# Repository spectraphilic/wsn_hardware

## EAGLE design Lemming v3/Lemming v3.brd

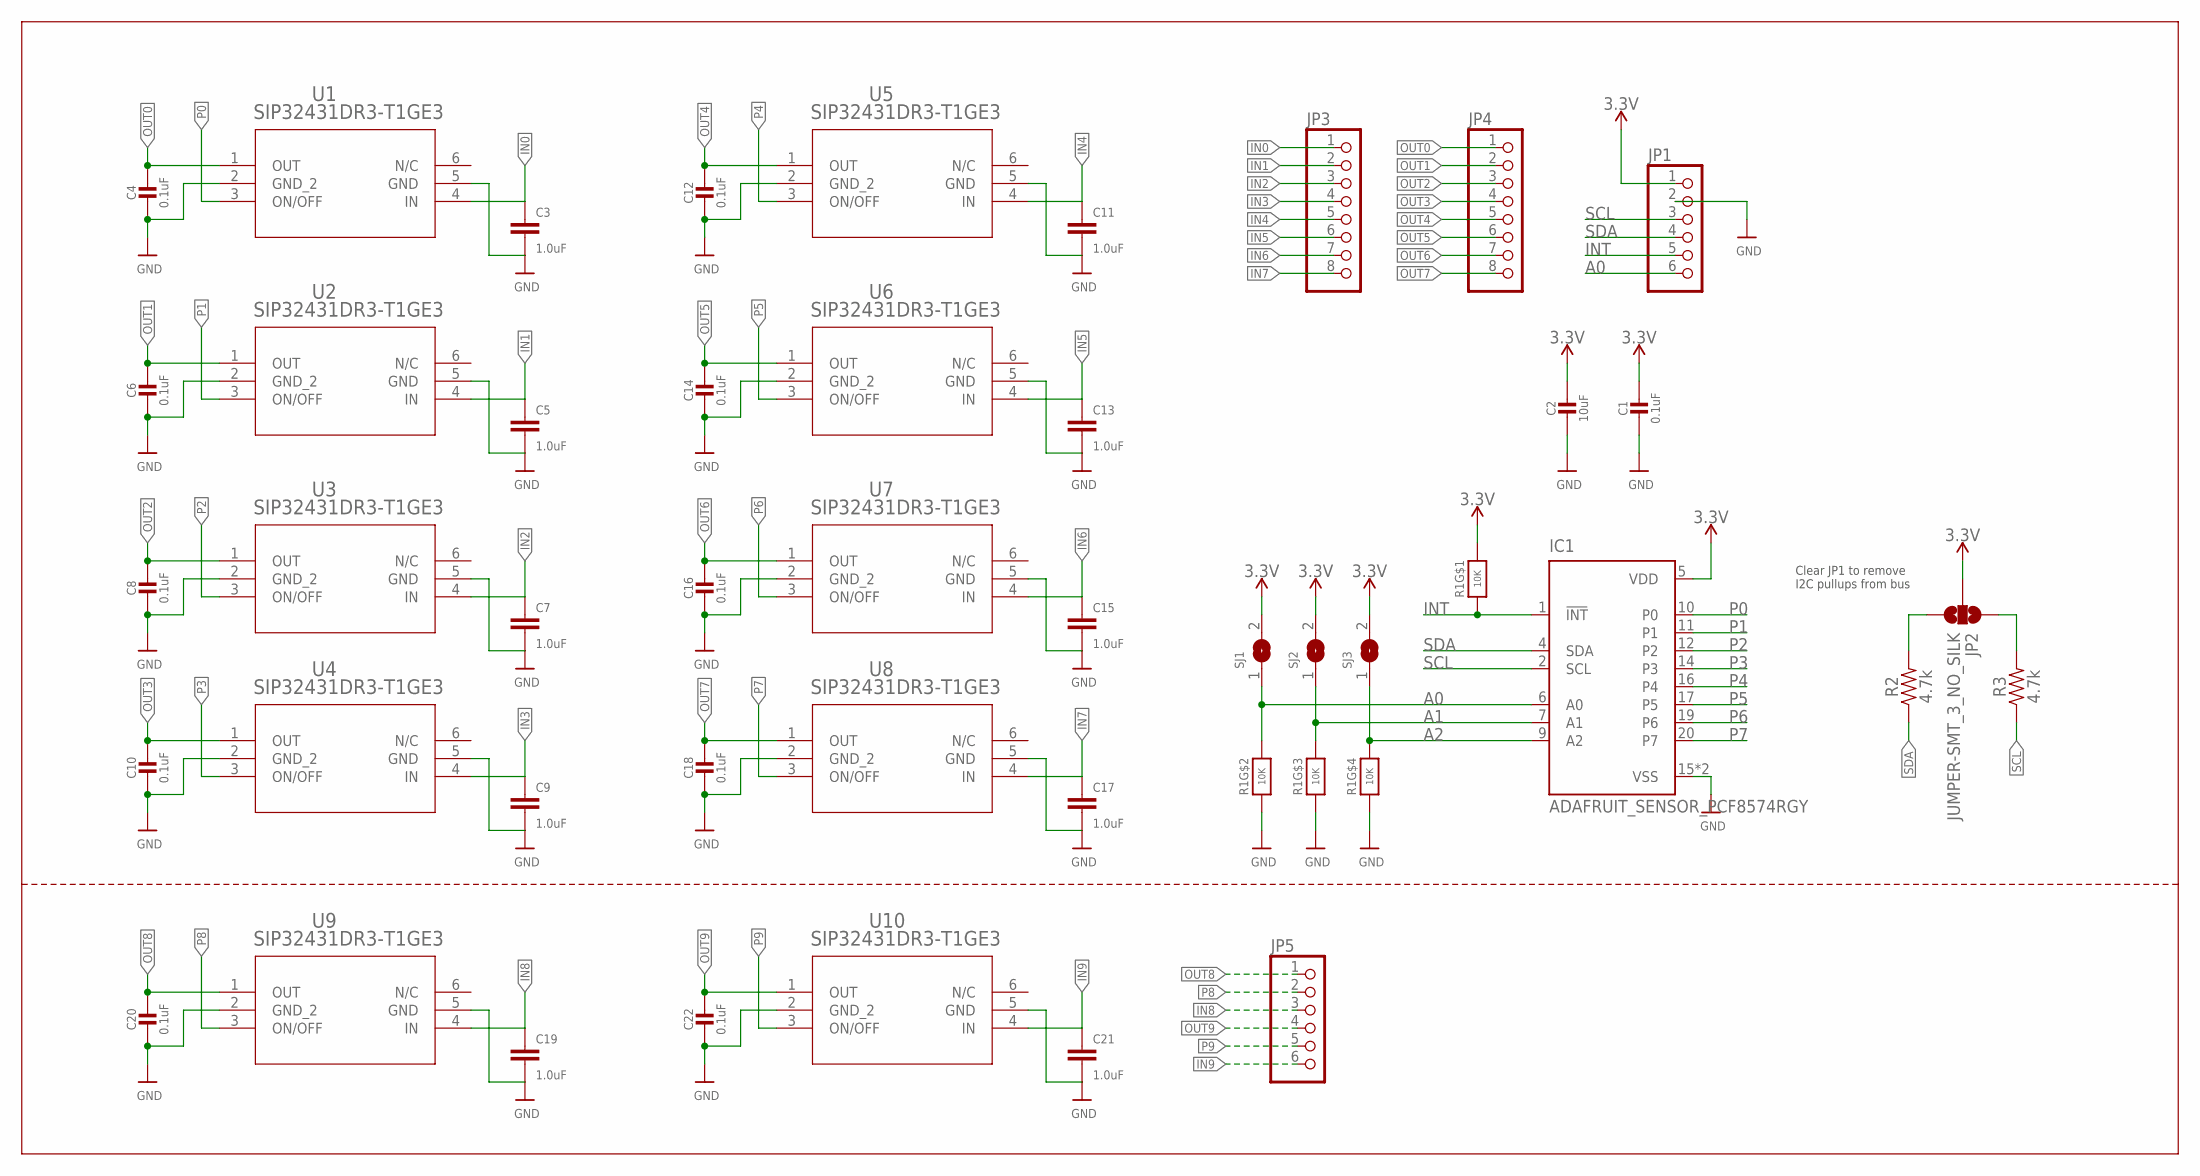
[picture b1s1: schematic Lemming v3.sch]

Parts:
C1, C4, C6, C8, C10, C12, C14, C16, C18, C20, C22: 0.1uF; 0603-NO
C2: 10uF; 0805-NO
C3, C5, C7, C9, C11, C13, C15, C17, C19, C21: 1.0uF; 0603
IC1: ADAFRUIT_SENSOR_PCF8574RGY; ADAFRUIT_SENSOR_VQFN20_3.5X4.5
JP1, JP5: HEADER-1X670MIL; 1X06_ROUND_70
JP2: JUMPER-SMT_3_NO_SILK; SMT-JUMPER_3_NO_SILK
JP3, JP4: PINHD-1X8BIG; 1X08-BIG
R1: 10K; MICROBUILDER_RESPACK_4X0603
R2, R3: 4.7k; 0603
SJ1, SJ2, SJ3: SOLDERJUMPER; SOLDERJUMPER_ARROW_NOPASTE
U1, U2, U3, U4, U5, U6, U7, U8, U9, U10: SIP32431DR3-T1GE3; SC-70-6_VIS

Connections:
3.3V: C1.1, C2.1, IC1.5 (VDD), JP1.1, JP2.2, R1.8 (2), SJ1.2, SJ2.2, SJ3.2
A0: IC1.6 (A0), JP1.6, R1.7 (2), SJ1.1
A1: IC1.7 (A1), R1.6 (2), SJ2.1
A2: IC1.9 (A2), R1.5 (2), SJ3.1
GND: C1.2, C2.2, C3.2, C4.2, C5.2, C6.2, C7.2, C8.2, C9.2, C10.2, C11.2, C12.2, C13.2, C14.2, C15.2, C16.2, C17.2, C18.2, C19.2, C20.2, C21.2, C22.2, IC1.15 (VSS), IC1.21 (VSS), JP1.2, R1.2 (1), R1.3 (1), R1.4 (1), U1.2 (GND_2), U1.5 (GND), U2.2 (GND_2), U2.5 (GND), U3.2 (GND_2), U3.5 (GND), U4.2 (GND_2), U4.5 (GND), U5.2 (GND_2), U5.5 (GND), U6.2 (GND_2), U6.5 (GND), U7.2 (GND_2), U7.5 (GND), U8.2 (GND_2), U8.5 (GND), U9.2 (GND_2), U9.5 (GND), U10.2 (GND_2), U10.5 (GND)
IN0: C3.1, JP3.1, U1.4 (IN)
IN1: C5.1, JP3.2, U2.4 (IN)
IN2: C7.1, JP3.3, U3.4 (IN)
IN3: C9.1, JP3.4, U4.4 (IN)
IN4: C11.1, JP3.5, U5.4 (IN)
IN5: C13.1, JP3.6, U6.4 (IN)
IN6: C15.1, JP3.7, U7.4 (IN)
IN7: C17.1, JP3.8, U8.4 (IN)
IN8: C19.1, JP5.3, U9.4 (IN)
IN9: C21.1, JP5.6, U10.4 (IN)
INT: IC1.1 (!INT), JP1.5, R1.1
unnamed: JP2.3, R2.2
unnamed: JP2.1, R3.2
OUT0: C4.1, JP4.1, U1.1 (OUT)
OUT1: C6.1, JP4.2, U2.1 (OUT)
OUT2: C8.1, JP4.3, U3.1 (OUT)
OUT3: C10.1, JP4.4, U4.1 (OUT)
OUT4: C12.1, JP4.5, U5.1 (OUT)
OUT5: C14.1, JP4.6, U6.1 (OUT)
OUT6: C16.1, JP4.7, U7.1 (OUT)
OUT7: C18.1, JP4.8, U8.1 (OUT)
OUT8: C20.1, JP5.1, U9.1 (OUT)
OUT9: C22.1, JP5.4, U10.1 (OUT)
P0: IC1.10 (P0), U1.3 (ON/OFF)
P1: IC1.11 (P1), U2.3 (ON/OFF)
P2: IC1.12 (P2), U3.3 (ON/OFF)
P3: IC1.14 (P3), U4.3 (ON/OFF)
P4: IC1.16 (P4), U5.3 (ON/OFF)
P5: IC1.17 (P5), U6.3 (ON/OFF)
P6: IC1.19 (P6), U7.3 (ON/OFF)
P7: IC1.20 (P7), U8.3 (ON/OFF)
P8: JP5.2, U9.3 (ON/OFF)
P9: JP5.5, U10.3 (ON/OFF)
SCL: IC1.2 (SCL), JP1.3, R3.1
SDA: IC1.4 (SDA), JP1.4, R2.1

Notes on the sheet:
Clear JP1 to remove I2C pullups from bus

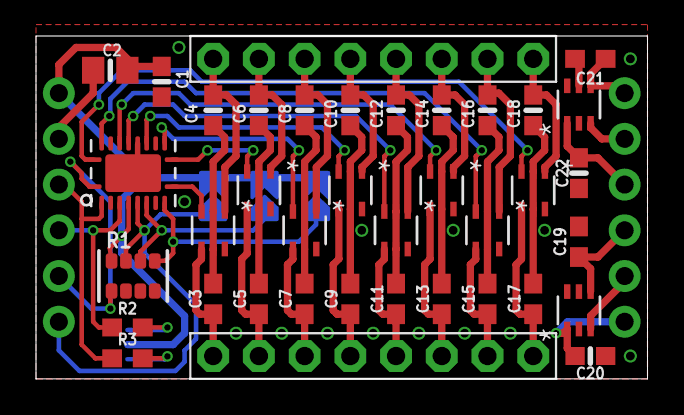
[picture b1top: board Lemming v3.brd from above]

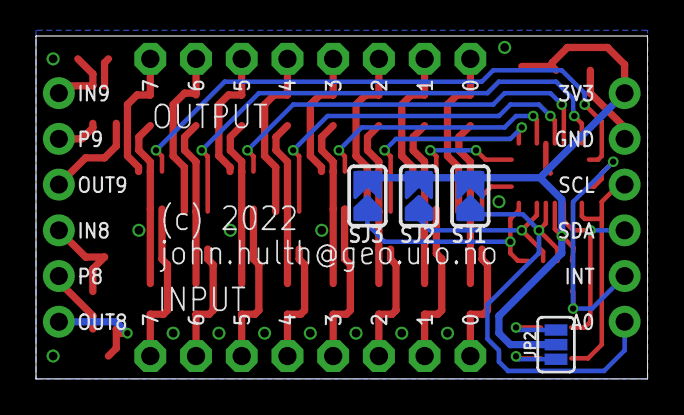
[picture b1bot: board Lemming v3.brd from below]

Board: 2 copper layers, 34.0 x 19.1 mm, 44 parts (4 on the bottom side), 40 nets.

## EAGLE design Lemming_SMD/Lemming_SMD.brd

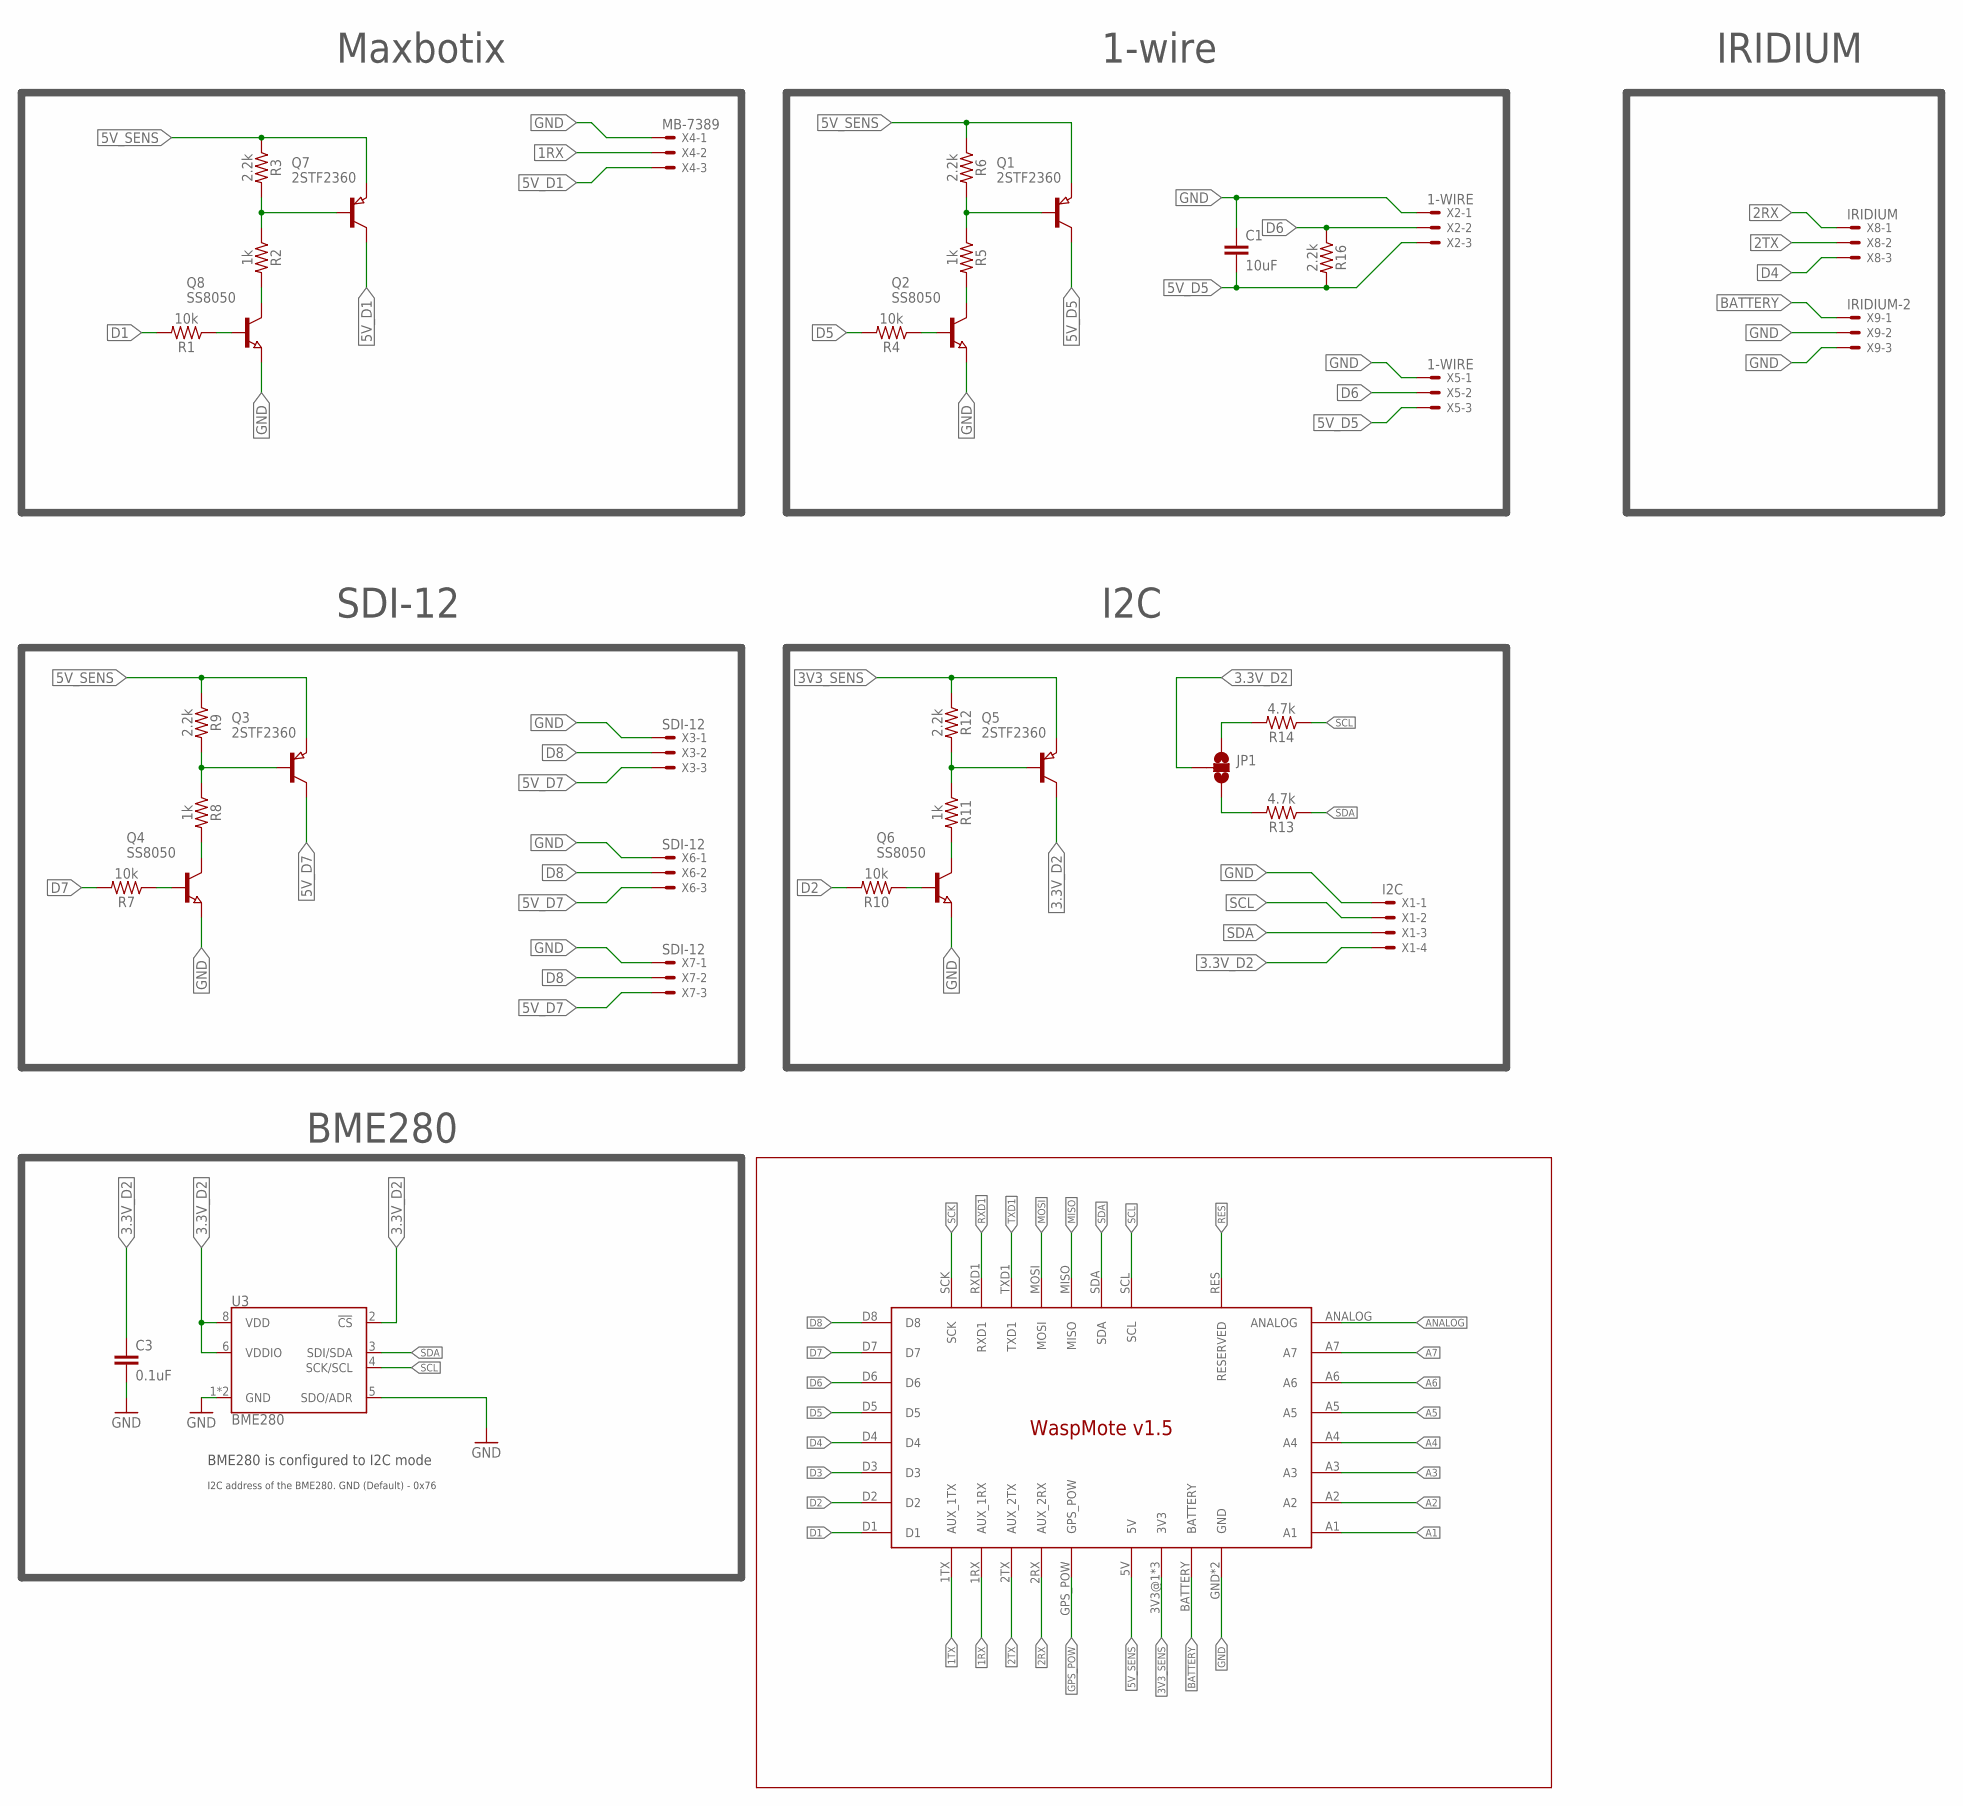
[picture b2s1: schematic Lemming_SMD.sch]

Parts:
C1: 10uF; 0603
C3: 0.1uF; 0603
JP1: JUMPER-SMT_3_NO_SILK; SMT-JUMPER_3_NO_SILK
Q1, Q3, Q5, Q7: 2STF2360; SOT89
Q2, Q4, Q6, Q8: SS8050; SOT23
R1, R4, R7, R10: 10k; 0603
R2, R5, R8, R11: 1k; 0603
R3, R6, R9, R12, R16: 2.2k; 0603
R13, R14: 4.7k; 0603
U3: BME280; LGA-8-2.5X2.5
U$1: WASPMOTE_V1.5
X1: I2C; 22-23-2041
X2, X5: 1-WIRE; 22-23-2031
X3, X6, X7: SDI-12; 22-23-2031
X4: MB-7389; 22-23-2031
X8: IRIDIUM; 22-23-2031
X9: IRIDIUM-2; 22-23-2031

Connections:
1RX: U$1.1RX (AUX_1RX), X4.2
1TX: U$1.1TX (AUX_1TX)
2RX: U$1.2RX (AUX_2RX), X8.1
2TX: U$1.2TX (AUX_2TX), X8.2
3.3V_D2: C3.1, JP1.2, Q5.2 (C), U3.2 (!CS), U3.6 (VDDIO), U3.8 (VDD), X1.4
3V3_SENS: Q5.3 (E), R12.1, U$1.3V3@1 (3V3), U$1.3V3@2 (3V3), U$1.3V3@3 (3V3)
5V_D1: Q7.2 (C), X4.3
5V_D5: C1.2, Q1.2 (C), R16.2, X2.3, X5.3
5V_D7: Q3.2 (C), X3.3, X6.3, X7.3
5V_SENS: Q1.3 (E), Q3.3 (E), Q7.3 (E), R3.1, R6.1, R9.1, U$1.5V
A1: U$1.A1
A2: U$1.A2
A3: U$1.A3
A4: U$1.A4
A5: U$1.A5
A6: U$1.A6
A7: U$1.A7
ANALOG: U$1.ANALOG
BATTERY: U$1.BATTERY, X9.1
D1: R1.2, U$1.D1
D2: R10.2, U$1.D2
D3: U$1.D3
D4: U$1.D4, X8.3
D5: R4.2, U$1.D5
D6: R16.1, U$1.D6, X2.2, X5.2
D7: R7.2, U$1.D7
D8: U$1.D8, X3.2, X6.2, X7.2
GND: C1.1, C3.2, Q2.2 (E), Q4.2 (E), Q6.2 (E), Q8.2 (E), U3.1 (GND), U3.5 (SDO/ADR), U3.7 (GND), U$1.GND, U$1.GND_2 (GND), X1.1, X2.1, X3.1, X4.1, X5.1, X6.1, X7.1, X9.2, X9.3
GPS_POW: U$1.GPS_POW
MISO: U$1.MISO
MOSI: U$1.MOSI
unnamed: Q6.1 (B), R10.1
unnamed: Q6.3 (C), R11.2
unnamed: Q5.1 (B), R11.1, R12.2
unnamed: Q2.1 (B), R4.1
unnamed: Q1.1 (B), R5.1, R6.2
unnamed: JP1.3, R13.2
unnamed: Q3.1 (B), R8.1, R9.2
unnamed: Q4.3 (C), R8.2
unnamed: Q4.1 (B), R7.1
unnamed: Q8.1 (B), R1.1
unnamed: Q8.3 (C), R2.2
unnamed: Q7.1 (B), R2.1, R3.2
unnamed: Q2.3 (C), R5.2
unnamed: JP1.1, R14.2
RES: U$1.RES (RESERVED)
RXD1: U$1.RXD1
SCK: U$1.SCK
SCL: R14.1, U3.4 (SCK/SCL), U$1.SCL, X1.2
SDA: R13.1, U3.3 (SDI/SDA), U$1.SDA, X1.3
TXD1: U$1.TXD1

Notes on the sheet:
Maxbotix
SDI-12
1-wire
I2C
I2C address of the BME280. GND (Default) - 0x76
BME280 is configured to I2C mode
BME280
IRIDIUM

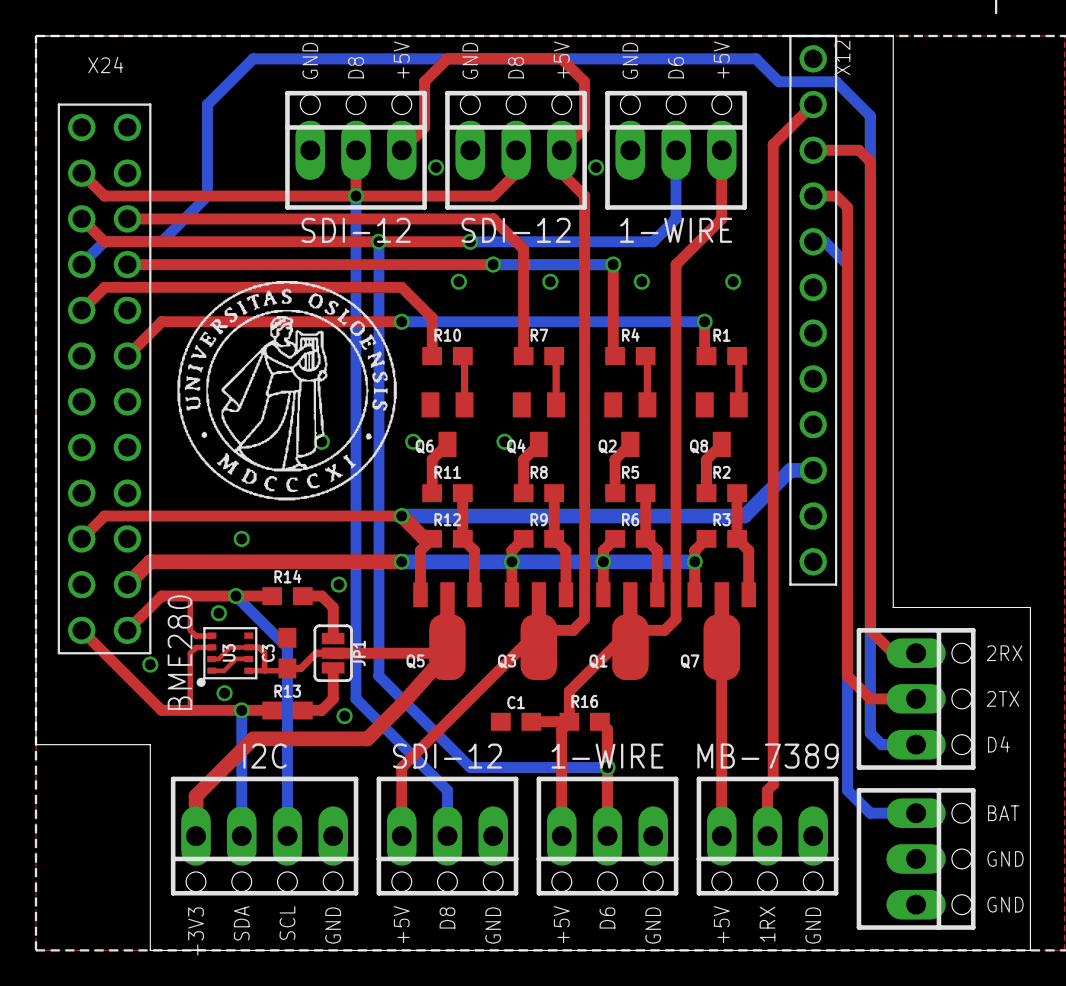
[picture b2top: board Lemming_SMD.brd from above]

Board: 2 copper layers, 55.2 x 50.8 mm, 38 parts (0 on the bottom side), 34 nets.

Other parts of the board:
U$3: UIO-LOGO-BL

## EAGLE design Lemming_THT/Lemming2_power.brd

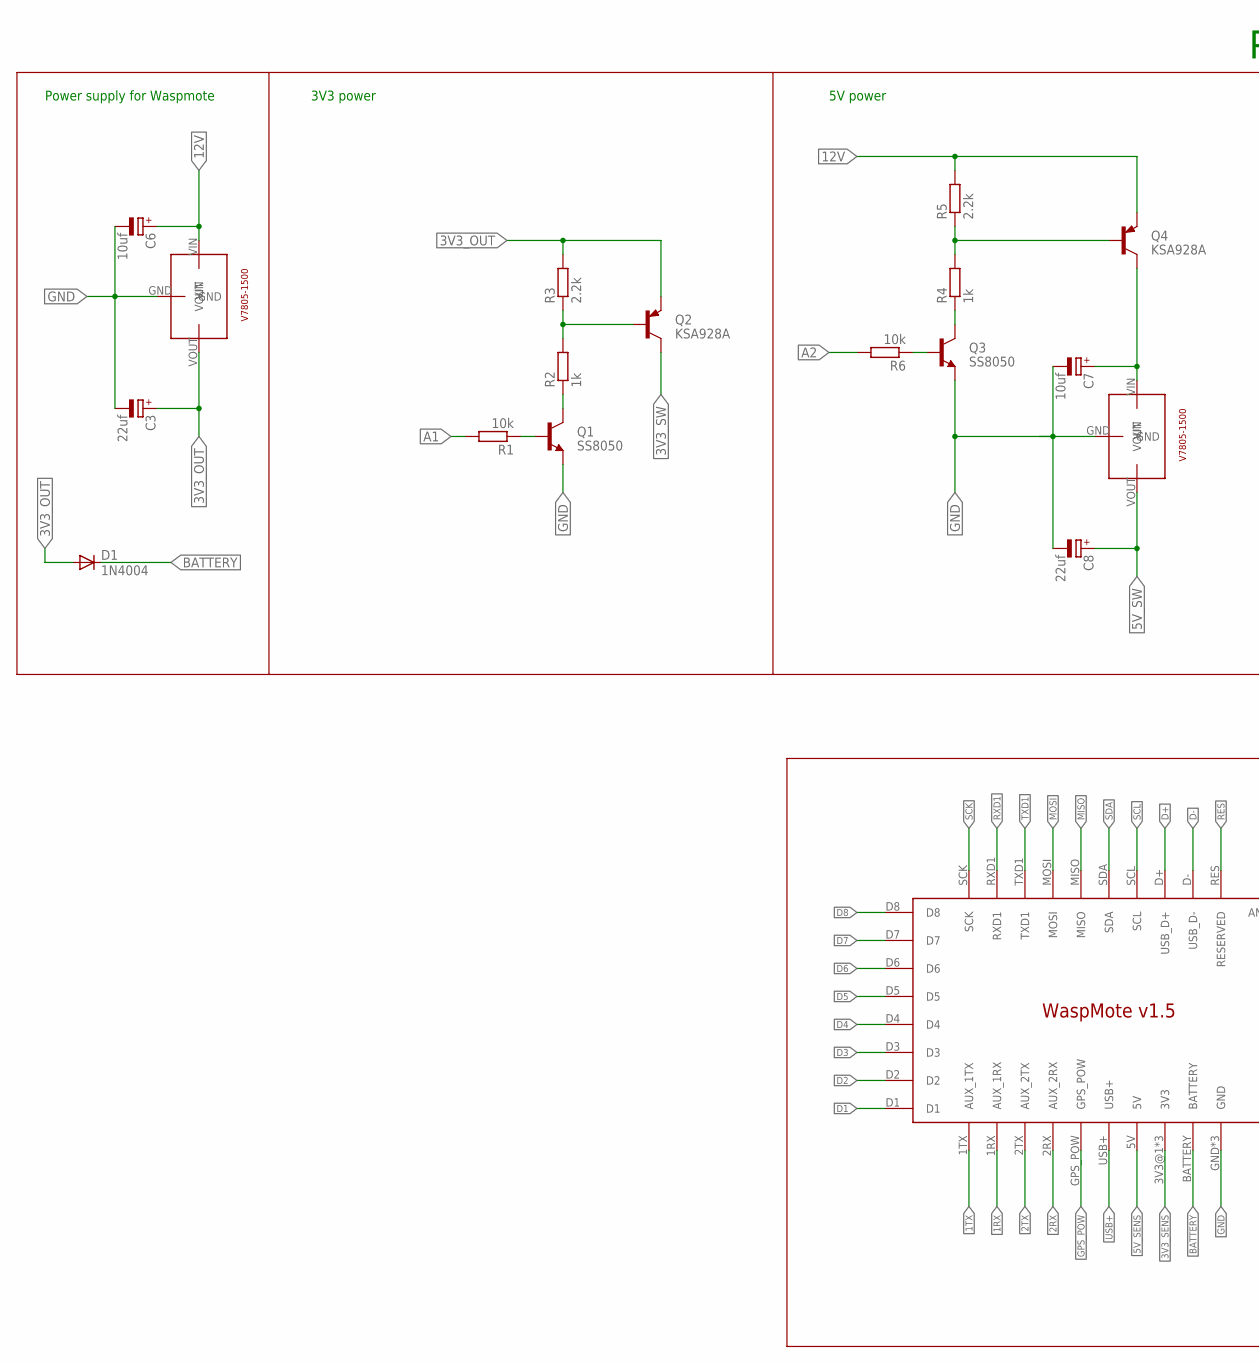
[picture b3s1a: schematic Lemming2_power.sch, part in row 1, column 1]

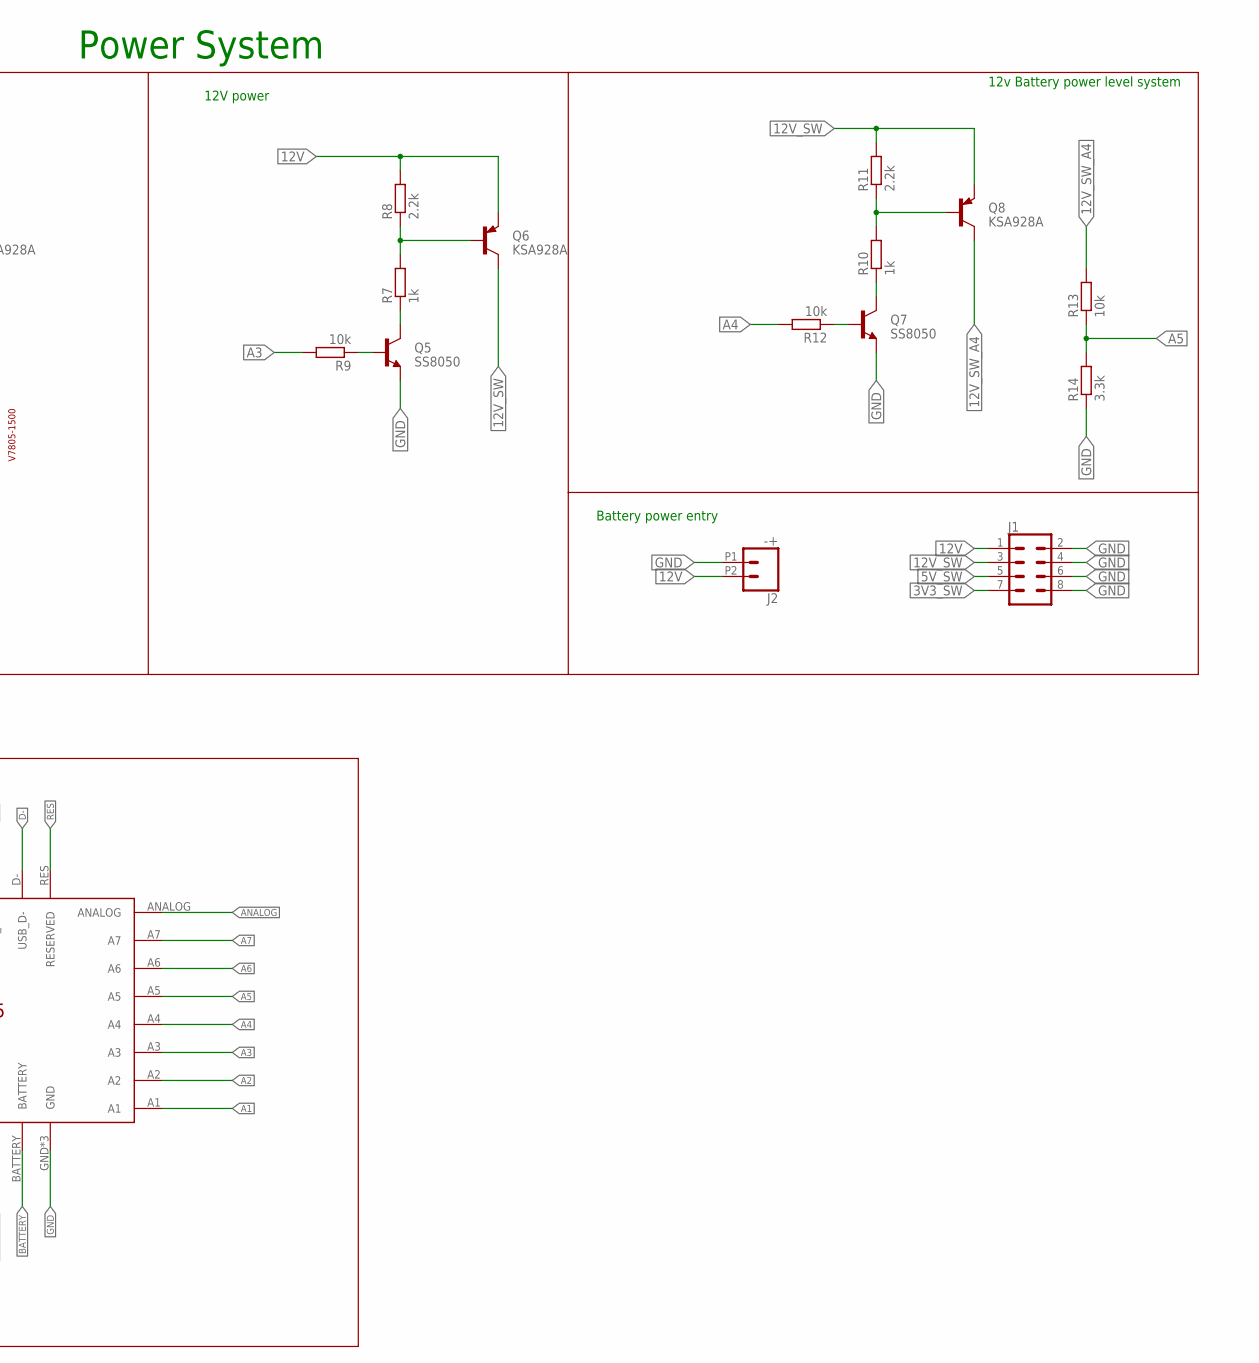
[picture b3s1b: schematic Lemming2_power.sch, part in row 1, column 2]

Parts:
C3, C8: 22uf; E2,5-5
C6, C7: 10uf; E2,5-5
D1: 1N4004; DO41-10
J1: CONN_04X2; 2X4
J2: -+; 1X02_2.54_SCREWTERM
LM7805: V7805-1500
Q1, Q3, Q5, Q7: SS8050; TO-92-EBC
Q2, Q4, Q6, Q8: KSA928A; TO-92-ECB
R1, R6, R9, R12, R13: 10k; RESISTOR_0309/10
R2, R4, R7, R10: 1k; RESISTOR_0309/10
R3, R5, R8, R11: 2.2k; RESISTOR_0309/10
R14: 3.3k; RESISTOR_0309/10
U$1: WASPMOTE_V1.5
U$22: V7803-1500; V7805-1500

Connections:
1RX: U$1.1RX (AUX_1RX)
1TX: U$1.1TX (AUX_1TX)
2RX: U$1.2RX (AUX_2RX)
2TX: U$1.2TX (AUX_2TX)
3V3_OUT: C3.+, D1.A, Q2.E, R3.2, U$22.VOUT
3V3_SENS: U$1.3V3@1 (3V3), U$1.3V3@2 (3V3), U$1.3V3@3 (3V3)
3V3_SW: J1.7, Q2.C
5V_SENS: U$1.5V
5V_SW: C8.+, J1.5, LM7805.VOUT
12V: C6.+, J1.1, J2.P2 (2), Q4.E, Q6.E, R5.2, R8.2, U$22.VIN
12V_SW: J1.3, Q6.C, Q8.E, R11.2
12V_SW_A4: Q8.C, R13.2
A1: R1.2, U$1.A1
A2: R6.2, U$1.A2
A3: R9.2, U$1.A3
A4: R12.2, U$1.A4
A5: R13.1, R14.2, U$1.A5
A6: U$1.A6
A7: U$1.A7
ANALOG: U$1.ANALOG
BATTERY: D1.C, U$1.BATTERY
D1: U$1.D1
D2: U$1.D2
D3: U$1.D3
D4: U$1.D4
D5: U$1.D5
D6: U$1.D6
D7: U$1.D7
D8: U$1.D8
D+: U$1.D+ (USB_D+)
D-: U$1.D- (USB_D-)
GND: C3.-, C6.-, C7.-, C8.-, J1.2, J1.4, J1.6, J1.8, J2.P1 (1), LM7805.GND, Q1.E, Q3.E, Q5.E, Q7.E, R14.1, U$1.GND, U$1.GND_2 (GND), U$1.USB- (GND), U$22.GND
GPS_POW: U$1.GPS_POW
MISO: U$1.MISO
MOSI: U$1.MOSI
unnamed: Q2.B, R2.2, R3.1
unnamed: Q1.C, R2.1
unnamed: Q1.B, R1.1
unnamed: Q6.B, R7.2, R8.1
unnamed: Q4.B, R4.2, R5.1
unnamed: Q5.C, R7.1
unnamed: Q5.B, R9.1
unnamed: Q3.C, R4.1
unnamed: Q3.B, R6.1
unnamed: Q8.B, R10.2, R11.1
unnamed: Q7.C, R10.1
unnamed: Q7.B, R12.1
unnamed: C7.+, LM7805.VIN, Q4.C
RES: U$1.RES (RESERVED)
RXD1: U$1.RXD1
SCK: U$1.SCK
SCL: U$1.SCL
SDA: U$1.SDA
TXD1: U$1.TXD1
USB+: U$1.USB+

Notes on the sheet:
12v Battery power level system
5V power
12V power
Battery power entry
Power supply for Waspmote
Power System
3V3 power

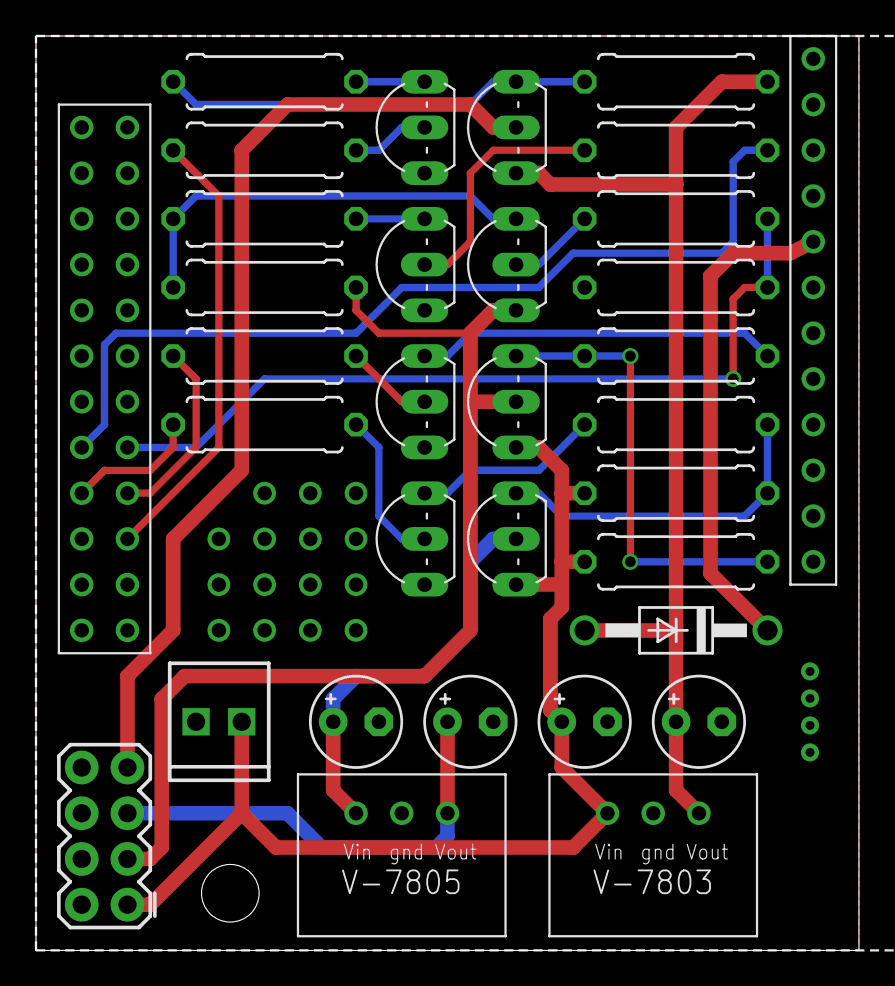
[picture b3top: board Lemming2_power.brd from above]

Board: 2 copper layers, 45.7 x 50.8 mm, 32 parts (0 on the bottom side), 27 nets.

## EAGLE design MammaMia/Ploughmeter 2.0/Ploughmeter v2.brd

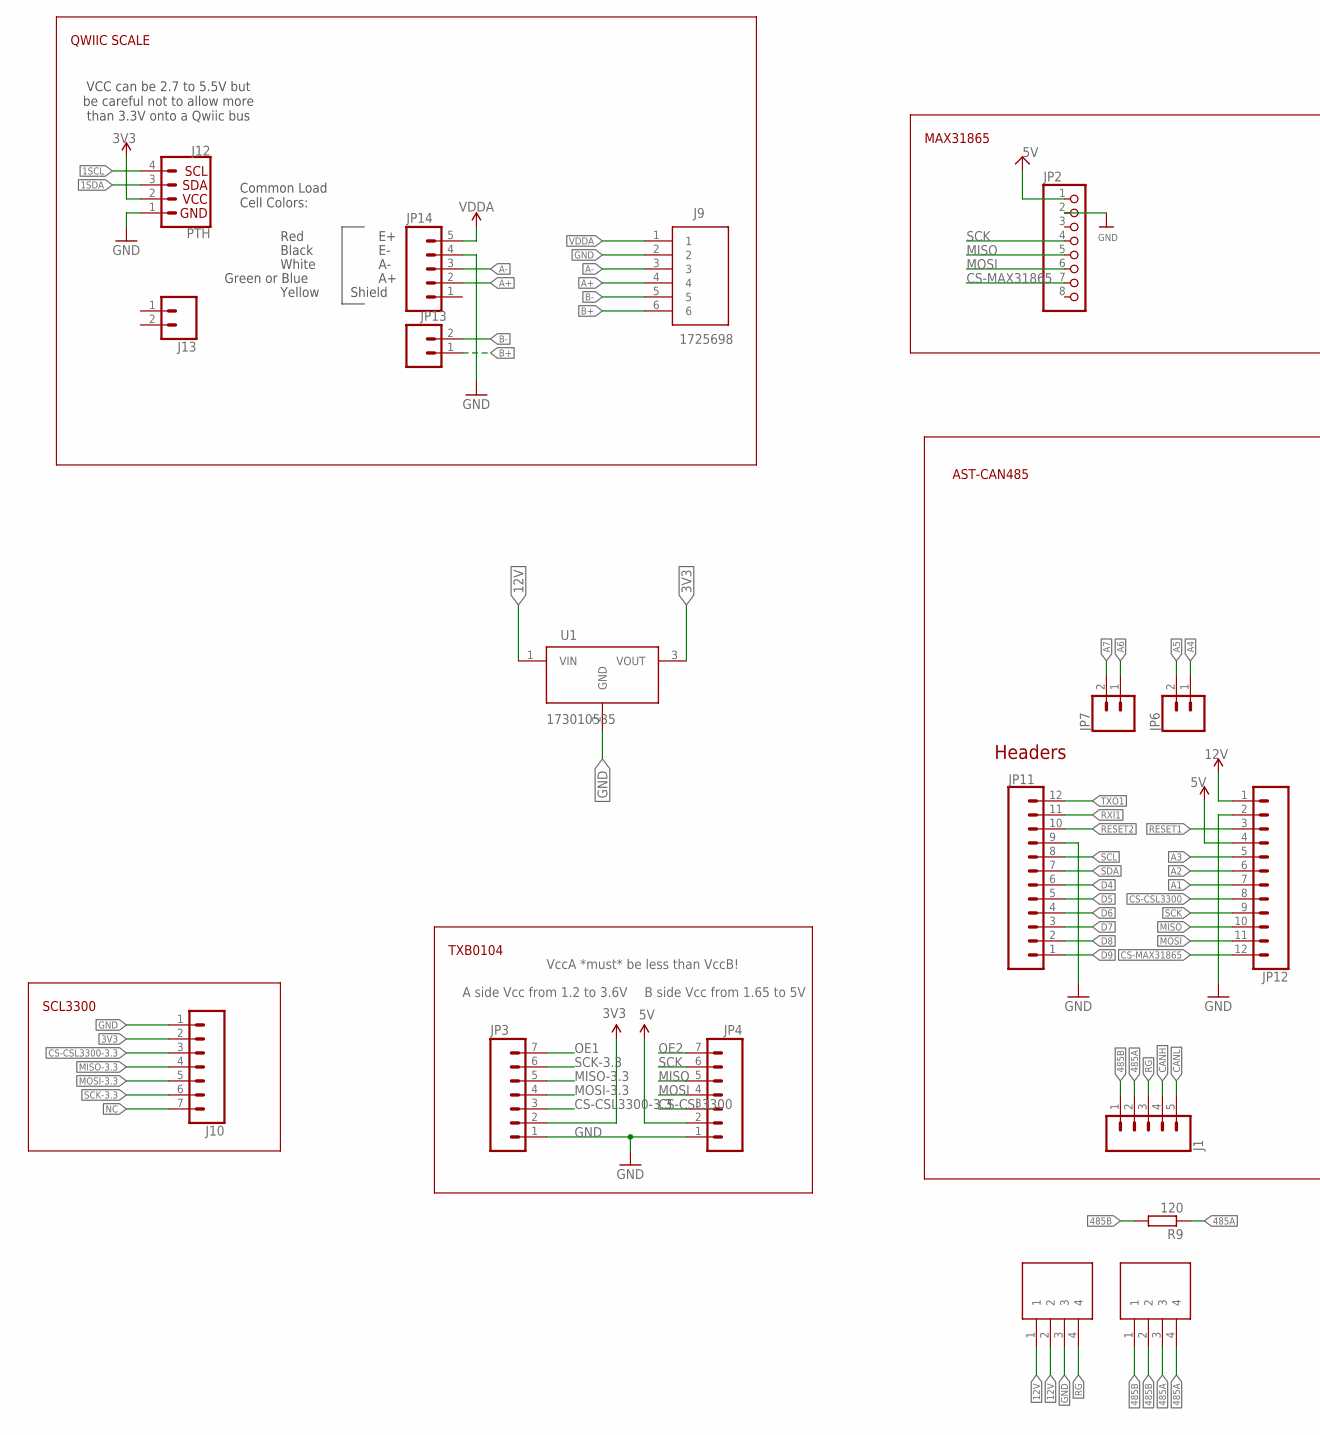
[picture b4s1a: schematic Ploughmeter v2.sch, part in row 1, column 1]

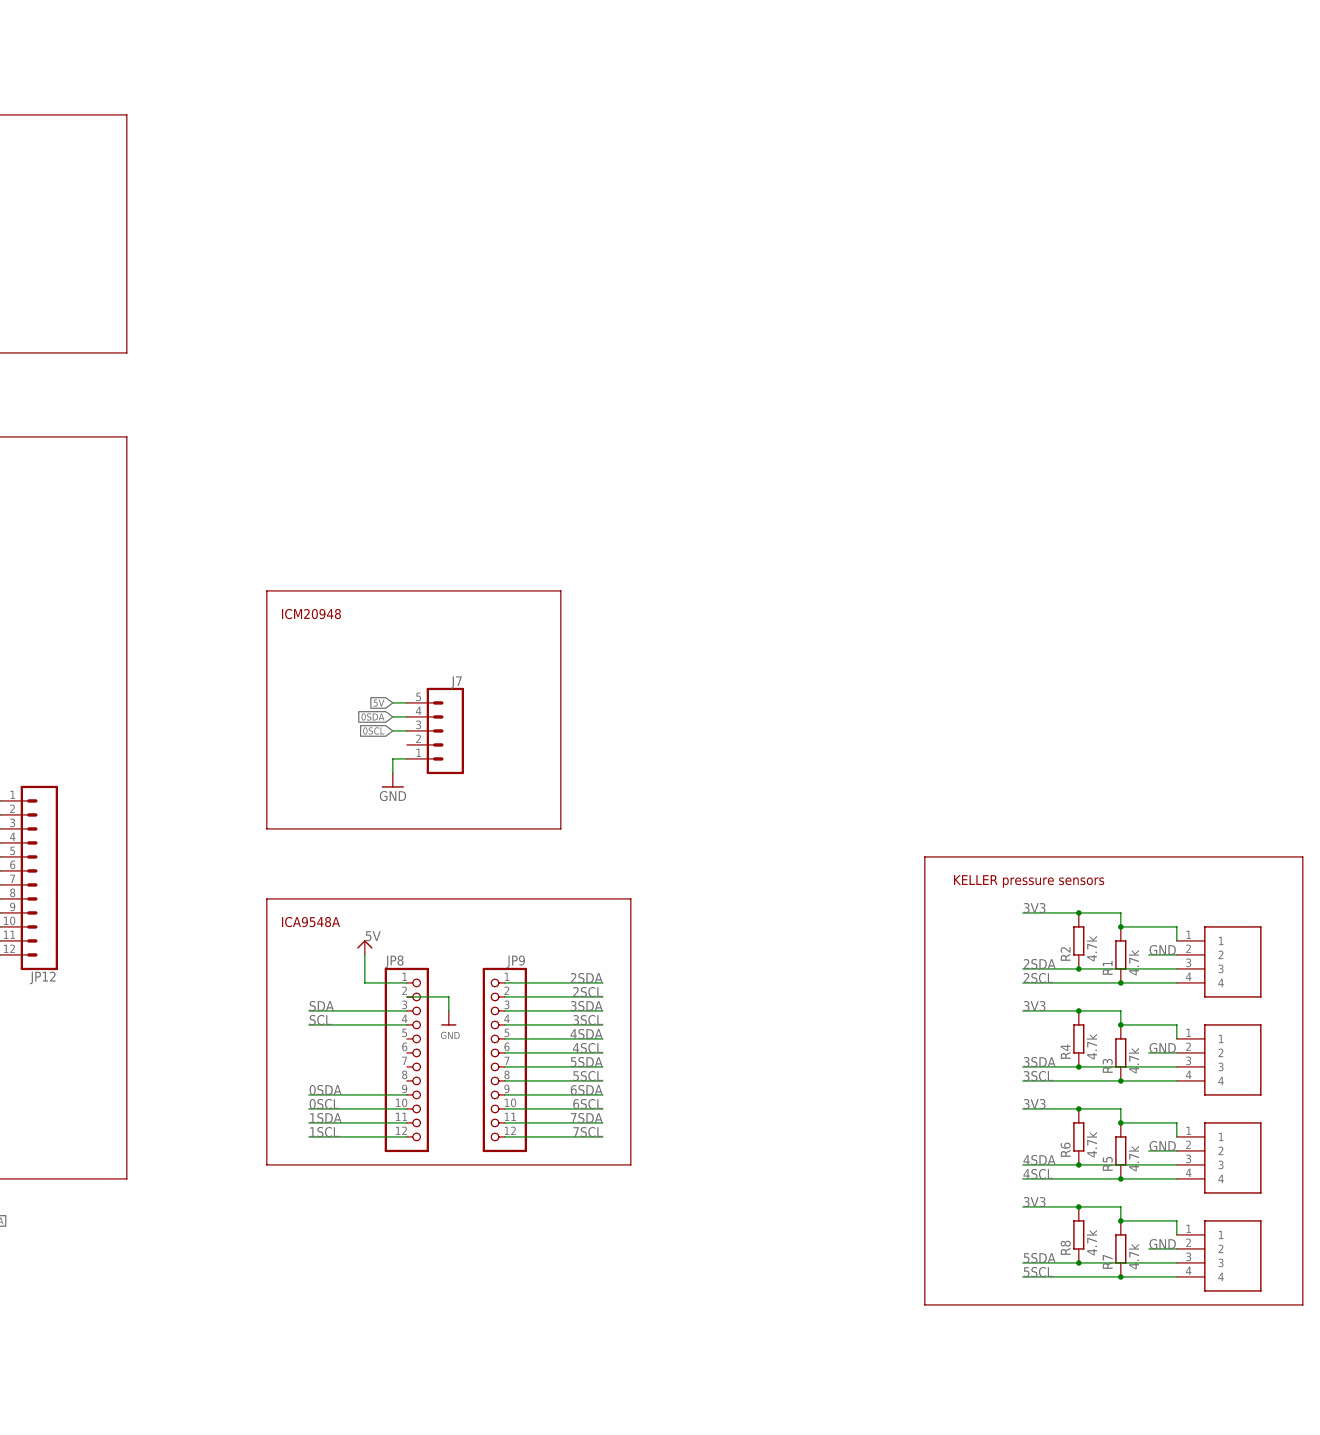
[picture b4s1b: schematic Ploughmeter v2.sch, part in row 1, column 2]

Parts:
J1, J7: CONN_05NO_SILK; 1X05_NO_SILK
J2, J3, J4, J5, J6, J8: 1725672; 1725672-4-2.54
J9: 1725698; SHDR6W90P0X254_1X6_1570X620X85
J10: CONN_07; 1X07
J12: PTH; 1X04_NO_SILK
J13: CONN_021X02_NO_SILK; 1X02_NO_SILK
JP2: HEADER-1X870MIL; 1X08_ROUND_70
JP3, JP4: M07; 1X07
JP6, JP7, JP13: CONN_021X02_NO_SILK; 1X02_NO_SILK
JP8, JP9: HEADER-1X12; 1X12_ROUND
JP11, JP12: CONN_12NO_SILK; 1X12_NO_SILK
JP14: CONN_05NO_SILK; 1X05_NO_SILK
R1, R2, R3, R4, R5, R6, R7, R8: 4.7k; RESISTOR_0309/10
R9: 120; RESISTOR_0309/10
U1: 173010535

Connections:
0SCL: J7.3, JP8.10
0SDA: J7.4, JP8.9
1SCL: J12.4, JP8.12
1SDA: J12.3, JP8.11
2SCL: J3.4, JP9.2, R1.1
2SDA: J3.3, JP9.1, R2.1
3SCL: J2.4, JP9.4, R3.1
3SDA: J2.3, JP9.3, R4.1
3V3: J2.1, J3.1, J4.1, J5.1, J10.2, J12.2, JP3.2, R1.2, R2.2, R3.2, R4.2, R5.2, R6.2, R7.2, R8.2, U1.3 (VOUT)
4SCL: J4.4, JP9.6, R5.1
4SDA: J4.3, JP9.5, R6.1
5SCL: J5.4, JP9.8, R7.1
5SDA: J5.3, JP9.7, R8.1
5V: J7.5, JP2.1, JP4.2, JP8.1, JP12.4
6SCL: JP9.10
6SDA: JP9.9
7SCL: JP9.12
7SDA: JP9.11
12V: J6.1, J6.2, JP12.1, U1.1 (VIN)
485A: J1.2, J8.3, J8.4, R9.1
485B: J1.1, J8.1, J8.2, R9.2
A1: JP12.7
A2: JP12.6
A3: JP12.5
A4: JP6.1
A5: JP6.2
A6: JP7.1
A7: JP7.2
A+: J9.4, JP14.2
A-: J9.3, JP14.3
B+: J9.6, JP13.1
B-: J9.5, JP13.2
CANH: J1.4
CANL: J1.5
CS-CSL3300: JP4.3, JP12.8
CS-CSL3300-3.3: J10.3, JP3.3
CS-MAX31865: JP2.7, JP12.12
D4: JP11.6
D5: JP11.5
D6: JP11.4
D7: JP11.3
D8: JP11.2
D9: JP11.1
GND: J2.2, J3.2, J4.2, J5.2, J6.3, J7.1, J9.2, J10.1, J12.1, JP2.2, JP3.1, JP4.1, JP8.2, JP11.9, JP12.2, JP14.4, U1.2 (GND)
MISO: JP2.5, JP4.5, JP12.10
MISO-3.3: J10.4, JP3.5
MOSI: JP2.6, JP4.4, JP12.11
MOSI-3.3: J10.5, JP3.4
NC: J10.7
OE1: JP3.7
OE2: JP4.7
RESET1: JP12.3
RESET2: JP11.10
RG: J1.3, J6.4
RXI1: JP11.11
SCK: JP2.4, JP4.6, JP12.9
SCK-3.3: J10.6, JP3.6
SCL: JP8.4, JP11.8
SDA: JP8.3, JP11.7
TXO1: JP11.12
VDDA: J9.1, JP14.5

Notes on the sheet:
A side Vcc from 1.2 to 3.6V
B side Vcc from 1.65 to 5V
VccA *must* be less than VccB!
Headers
TXB0104
AST-CAN485
MAX31865
ICA9548A
KELLER pressure sensors
ICM20948
SCL3300
Red
Black
White
Green or Blue
Common Load Cell Colors:
Shield
Yellow
VCC can be 2.7 to 5.5V but be careful not to allow more than 3.3V onto a Qwiic bus
QWIIC SCALE

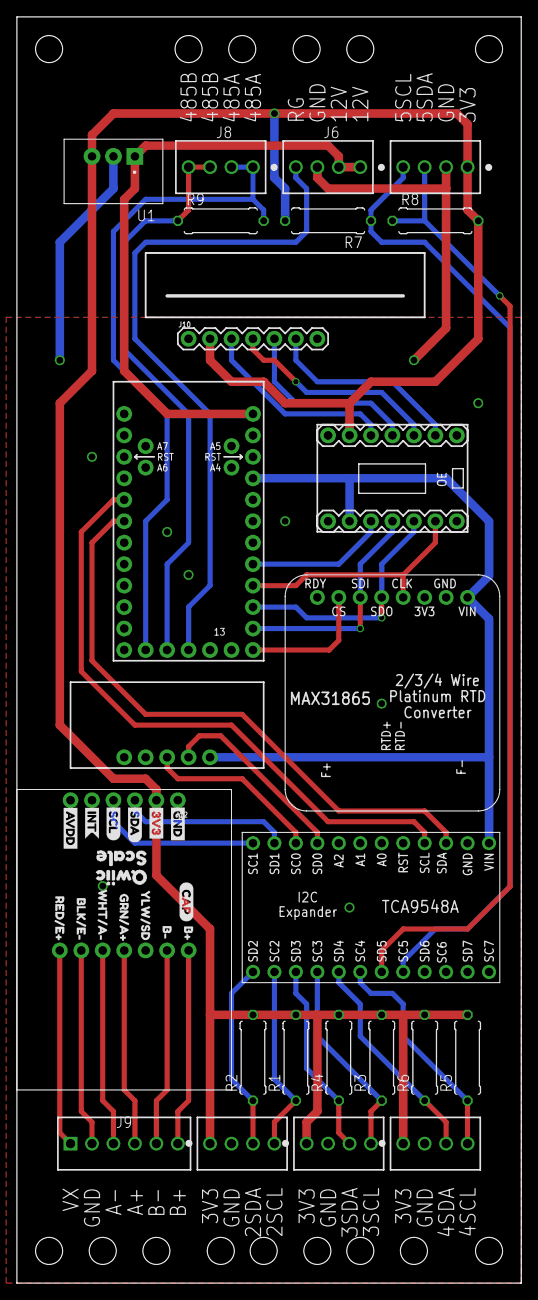
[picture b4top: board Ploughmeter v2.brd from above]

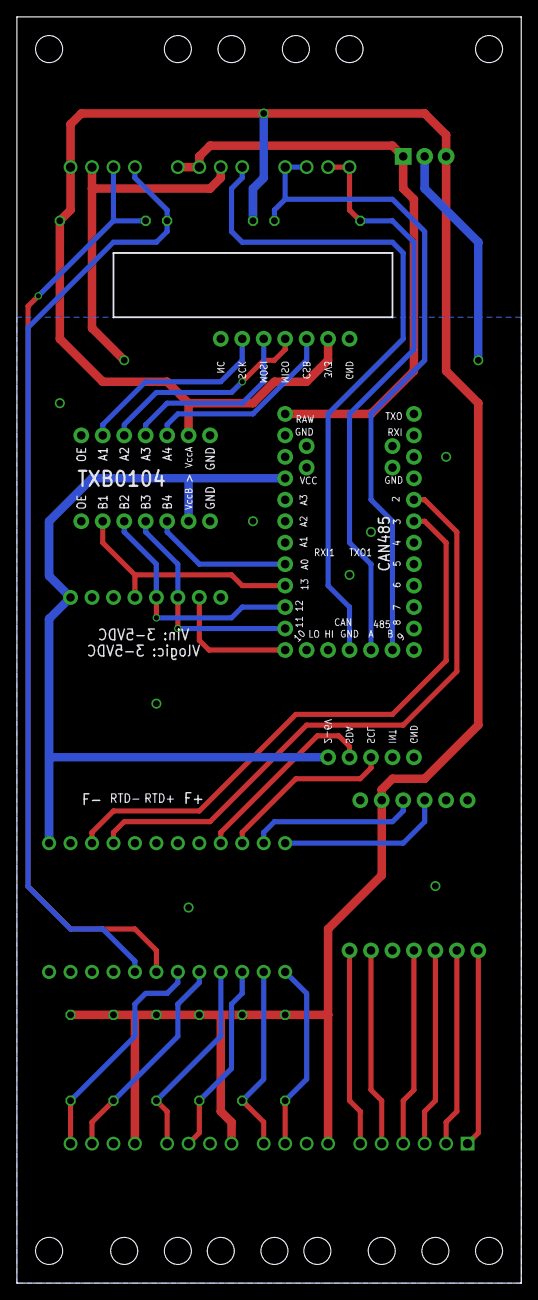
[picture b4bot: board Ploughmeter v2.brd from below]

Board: 2 copper layers, 59.7 x 149.9 mm, 49 parts (2 on the bottom side), 35 nets.

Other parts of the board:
U$10: SDA-[)
U$15: SCL-[)
U$16: 3V3-04
U$18: GND-04
U$19: B#11
U$22: B#12
U$23: BLK#E#1
U$24: GRN#A#4
U$25: RED#E#2
U$26: WHT#A#3
U$27: YLW#SD4
U$28: AVDD4
U$29: CAP0
U$30: QWIIC2
U$31: SCALE3
U$32: INT0

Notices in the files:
Lemming v3/Lemming v3.brd:
(c) 2022
Lemming_SMD/Lemming_SMD.brd:
(C) 2020
parts and their libraries:
microbuilder: This work is placed in the public domain, and may be freely used for commercial and non-commercial work with the following conditions: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
SparkFun-Resistors: Licensing: Creative Commons ShareAlike 4.0 International - https://creativecommons.org/licenses/by-sa/4.0
